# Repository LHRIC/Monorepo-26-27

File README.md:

# LHRIC Monorepo 26/27

This is the Monorepo containing all of the code for the LHRIC 26/27 season.
Documentation is hosted at a GitHub pages site for this repository. If you're
looking for a broad overview of projects look in the confluence and if you're
looking for specific details about implementations, look at the GitHub pages docs.

Check the [documentation website](https://lhric.github.io/Monorepo-26-27/) for more info.

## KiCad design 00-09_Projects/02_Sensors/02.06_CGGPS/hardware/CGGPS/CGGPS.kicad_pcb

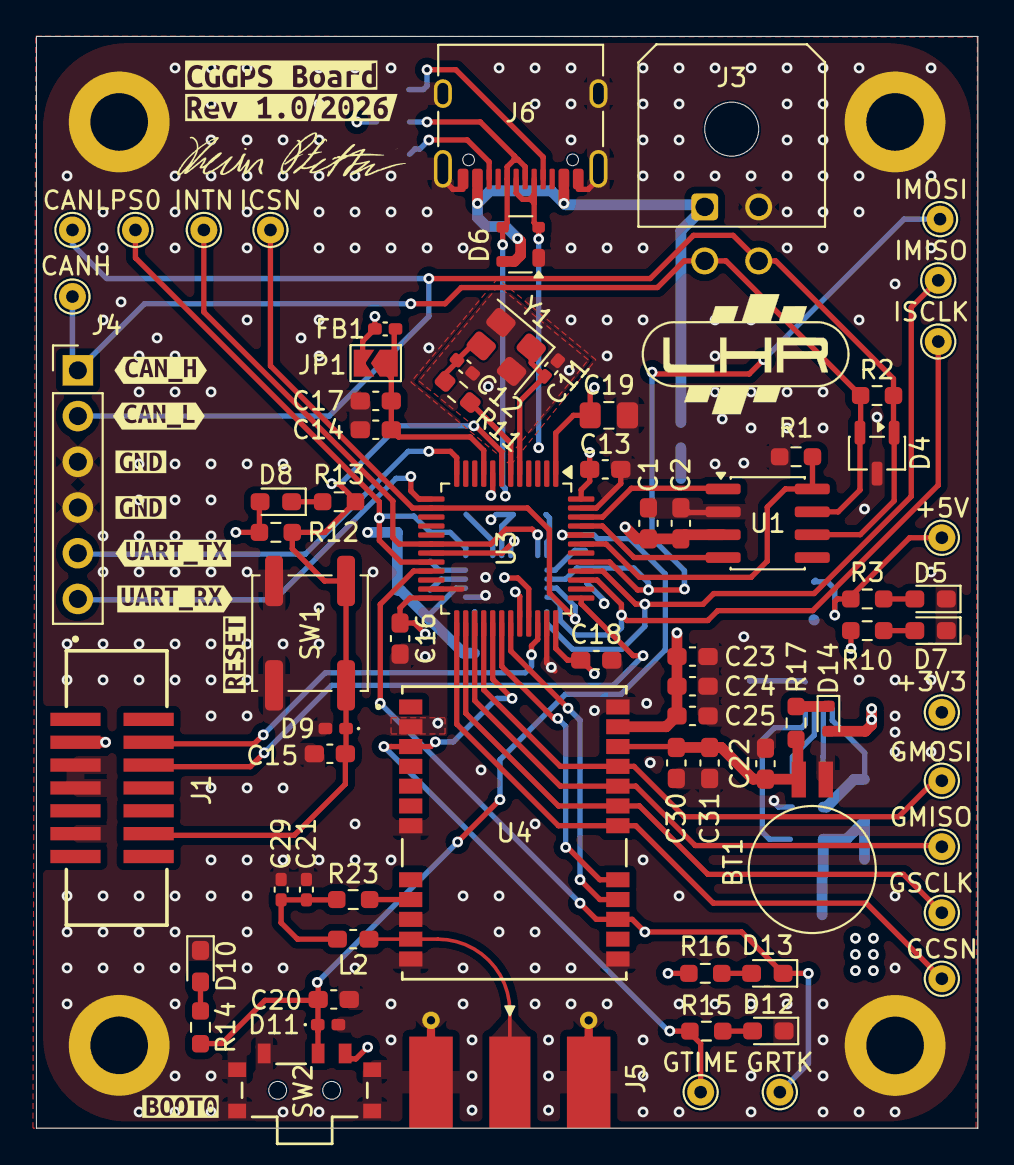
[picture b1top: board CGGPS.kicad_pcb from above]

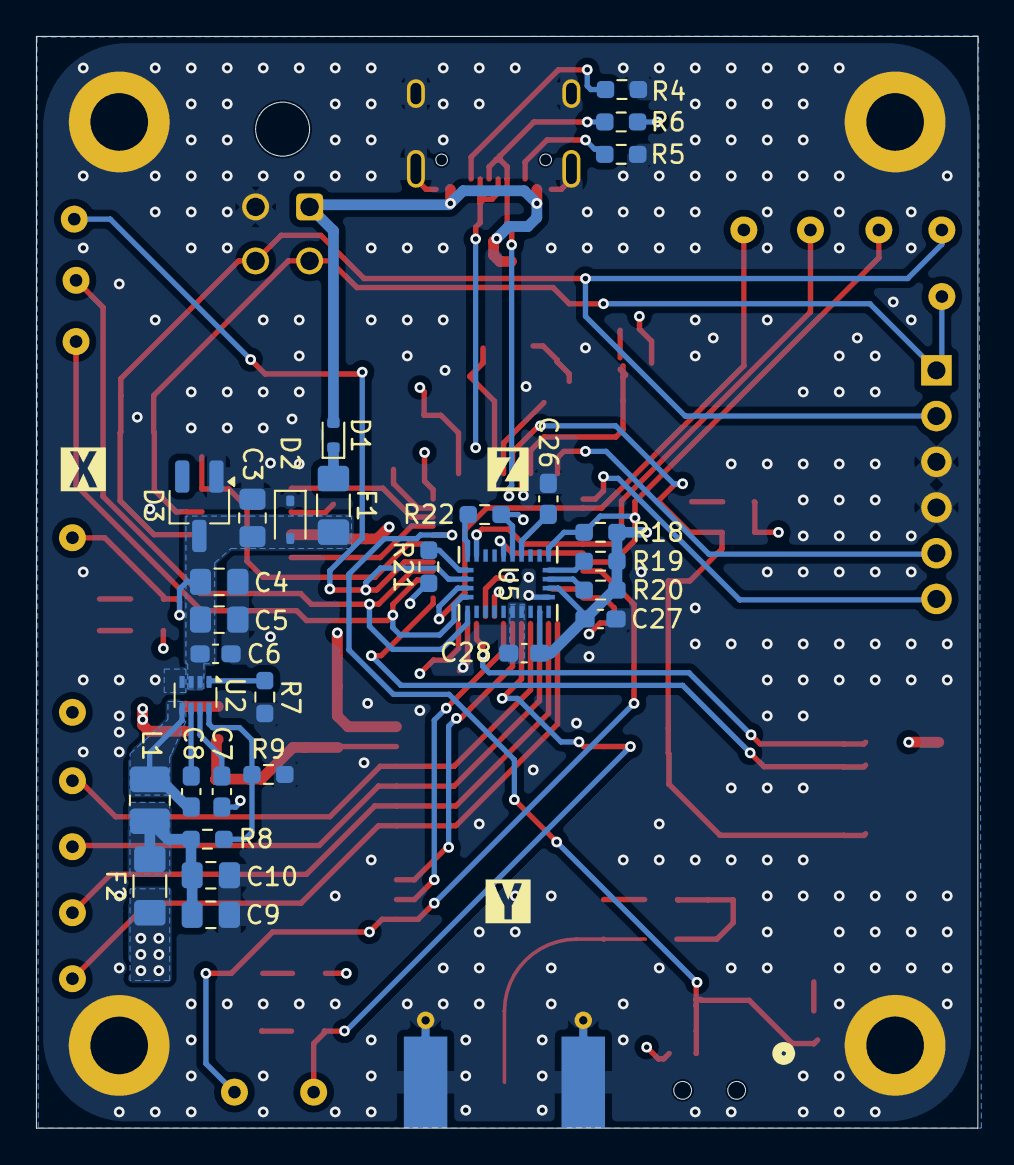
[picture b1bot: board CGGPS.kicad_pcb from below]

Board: 4 copper layers, 52.3 x 60.6 mm, 122 parts (33 on the bottom side), 61 nets.

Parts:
+3V3, +5V: TestPoint; TestPoint_THTPad_D1.5mm_Drill0.7mm
BT1: MS621FE-FL11E; BatteryHolder_Seiko_MS621F
C1, C6, C8, C13, C15, C16, C18, C20, C23, C24, C26, C27, C28: 0.1uF; C_0603_1608Metric_Pad1.08x0.95mm_HandSolder
C2, C17, C22, C25, C30, C31: 1uF; C_0603_1608Metric_Pad1.08x0.95mm_HandSolder
C3: 33uF; C_0805_2012Metric_Pad1.18x1.45mm_HandSolder
C4, C5: 10uF; C_0805_2012Metric_Pad1.18x1.45mm_HandSolder
C7: 33nF; C_0603_1608Metric_Pad1.08x0.95mm_HandSolder
C9, C10: 22uF; C_0805_2012Metric_Pad1.18x1.45mm_HandSolder
C11, C12: 12pF; C_0402_1005Metric_Pad0.74x0.62mm_HandSolder
C14: 10nF; C_0603_1608Metric_Pad1.08x0.95mm_HandSolder
C19: 4.7uF; C_0805_2012Metric_Pad1.18x1.45mm_HandSolder
C21: 47 pF; C_0402_1005Metric_Pad0.74x0.62mm_HandSolder
C29: 100nF; C_0402_1005Metric_Pad0.74x0.62mm_HandSolder
CANH: TestPoint; TestPoint_THTPad_D1.5mm_Drill0.7mm
CANL: TestPoint; TestPoint_THTPad_D1.5mm_Drill0.7mm
D1, D14: SDM20U30-7; D_SOD-523
D2: SD05C-01F; D_SOD-323
D3: SZBZX84C5V1LT1G; SC-59_Handsoldering
D4: ESD2CAN24DBZRQ1; SOT-23-3
D5, D7, D13: LED_GREEN; D_0603_1608Metric_Pad1.05x0.95mm_HandSolder
D6: PRTR5V0U2X; SOT-143
D8: LED_RED; D_0603_1608Metric_Pad1.05x0.95mm_HandSolder
D9, D11: ACPDQC3V3T-HF; D_0402_1005Metric_Pad0.77x0.64mm_HandSolder
D10: LED_AMBER; D_0603_1608Metric_Pad1.05x0.95mm_HandSolder
D12: LED_BLUE; D_0603_1608Metric_Pad1.05x0.95mm_HandSolder
F1: 0.5A; Fuse_1206_3216Metric_Pad1.42x1.75mm_HandSolder
F2: 750mA; Fuse_1206_3216Metric_Pad1.42x1.75mm_HandSolder
FB1: FerriteBead; L_0402_1005Metric_Pad0.77x0.64mm_HandSolder
GCSN: TestPoint; TestPoint_THTPad_D1.5mm_Drill0.7mm
GMISO: TestPoint; TestPoint_THTPad_D1.5mm_Drill0.7mm
GMOSI: TestPoint; TestPoint_THTPad_D1.5mm_Drill0.7mm
GRTK: TestPoint; TestPoint_THTPad_D1.5mm_Drill0.7mm
GSCLK: TestPoint; TestPoint_THTPad_D1.5mm_Drill0.7mm
GTIME: TestPoint; TestPoint_THTPad_D1.5mm_Drill0.7mm
H1, H2, H3, H4: MountingHole_Pad; MountingHole_3.2mm_M3_DIN965_Pad
ICSN: TestPoint; TestPoint_THTPad_D1.5mm_Drill0.7mm
IMISO: TestPoint; TestPoint_THTPad_D1.5mm_Drill0.7mm
IMOSI: TestPoint; TestPoint_THTPad_D1.5mm_Drill0.7mm
INTN: TestPoint; TestPoint_THTPad_D1.5mm_Drill0.7mm
ISCLK: TestPoint; TestPoint_THTPad_D1.5mm_Drill0.7mm
J1: SHF-107-01-L-D-SM; SAMTEC_SHF-107-01-L-D-SM
J3: Conn_01x04_Socket; Molex_Micro-Fit_3.0_43045-0400_2x02_P3.00mm_Horizontal
J4: Conn_01x06_Pin; PinHeader_1x06_P2.54mm_Vertical
J5: Conn_Coaxial; SMA_Molex_73251-1153_EdgeMount_Horizontal
J6: USB_C_Receptacle_USB2.0_16P; USB_C_Receptacle_XKB_U262-16XN-4BVC11
JP1: SolderJumper_2_Open; SolderJumper-2_P1.3mm_Open_TrianglePad1.0x1.5mm
L1: 1uH; L_1008_2520Metric_Pad1.43x2.20mm_HandSolder
L2: 120 nH; L_0603_1608Metric_Pad1.05x0.95mm_HandSolder
PS0: TestPoint; TestPoint_THTPad_D1.5mm_Drill0.7mm
R1, R7, R9, R12, R18, R19, R20: 10k; R_0603_1608Metric_Pad0.98x0.95mm_HandSolder
R2: 120; R_0603_1608Metric_Pad0.98x0.95mm_HandSolder
R3, R10, R13, R14: 330; R_0603_1608Metric_Pad0.98x0.95mm_HandSolder
R4, R5: 5.1k; R_0603_1608Metric_Pad0.98x0.95mm_HandSolder
R6: 1.5k; R_0603_1608Metric_Pad0.98x0.95mm_HandSolder
R8: 31.6k; R_0603_1608Metric_Pad0.98x0.95mm_HandSolder
R11, R15, R16: 220; R_0603_1608Metric_Pad0.98x0.95mm_HandSolder
R17: 620; R_0603_1608Metric_Pad0.98x0.95mm_HandSolder
R21, R22: 4.7k; R_0603_1608Metric_Pad0.98x0.95mm_HandSolder
R23: 15; R_0603_1608Metric_Pad0.98x0.95mm_HandSolder
SW1: PTS645SH43SMTR92 LFS; SW_Push_1P1T_NO_CK_KSC7xxJ
SW2: 450404015514; WS-SLSU_6p7x2p7_WRE
U1: SN65HVD230; SOIC-8_3.9x4.9mm_P1.27mm
U2: TPS62933DRLR; SOT-583-8
U3: STM32F302C8Tx; LQFP-48_7x7mm_P0.5mm
U4: NEO-F9P-15B
U5: BNO086; BN0086_1_LGA-28_CEV
Y1: RH100-16.000-9-1010-TR; Crystal_SMD_WE_CFPX-180-4Pin_3.2x2.5mm
kibuzzard-6AEAD634, kibuzzard-6AEAD634#2: G***; kibuzzard-6AEAD634
kibuzzard-6AEAD642: G***; kibuzzard-6AEAD642
kibuzzard-6AEAD654: G***; kibuzzard-6AEAD654
kibuzzard-6AEAD677: G***; kibuzzard-6AEAD677
kibuzzard-6AEAD693: G***; kibuzzard-6AEAD693
kibuzzard-6AEAD714: G***; kibuzzard-6AEAD714
kibuzzard-6AEADD88: G***; kibuzzard-6AEADD88
kibuzzard-6AEF8D4C: G***; kibuzzard-6AEF8D4C
kibuzzard-6AEF8E55: G***; kibuzzard-6AEF8E55
kibuzzard-6AEFA2AB: G***; kibuzzard-6AEFA2AB
kibuzzard-6AEFA2BC: G***; kibuzzard-6AEFA2BC
kibuzzard-6AEFA2C8: G***; kibuzzard-6AEFA2C8
kibuzzard-6AEFC3E2: G***; kibuzzard-6AEFC3E2

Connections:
+3.3V: +3V3.1 (1_1), C1.1, C2.1, C13.1, C16.1, C18.1, C19.1, C23.1, C24.1, C25.1, C27.1, C28.1, D8.2 (A), D14.2 (A), F2.2, FB1.2, J1.03, JP1.2 (B), R6.1, R10.1, R12.1, R16.1, R18.1, R19.1, R20.1, R21.1, R22.1, SW2.3 (A), U1.3 (VCC), U3.1 (VBAT), U3.24 (VDD), U3.36 (VDD), U3.48 (VDD), U4.23 (VCC), U5.3 (VDD), U5.10 (CLKSEL0), U5.28 (VDDIO)
+3.3VA: C14.1, C17.1, FB1.1, JP1.1 (A), U3.9 (VDDA)
+5V: +5V.1 (1_1), C3.1, C4.1, C5.1, C6.1, D2.2 (A2), D3.3 (K), F1.2, R3.1, U2.2 (EN), U2.3 (VIN)
+VBUS: D1.2 (A), D6.4 (VCC), J3.1, J6.A4 (VBUS), J6.A9 (VBUS), J6.B4 (VBUS), J6.B9 (VBUS)
/CAN_H: CANH.1 (1_1), D4.2, J3.3, J4.1, R2.1, U1.7 (CANH)
/CAN_L: CANL.1 (1_1), D4.1, J3.4, J4.2, R2.2, U1.6 (CANL)
/CAN_RX: U1.4 (R), U3.45 (PB8)
/CAN_SLEEP: R1.1, U1.8 (Rs), U3.43 (PB7)
/CAN_TX: U1.1 (D), U3.46 (PB9)
/GPS/V_BACKUP: BT1.1 (+), C22.1, C30.1, C31.1, R17.2, U4.22 (V_BCKP)
/GPS_CS_N: GCSN.1 (1_1), U3.25 (PB12), U4.18 (SDA/SPI_CS_N)
/GPS_MISO: GMISO.1 (1_1), U3.27 (PB14), U4.20 (TXD/SPI_SDO)
/GPS_MOSI: GMOSI.1 (1_1), U3.28 (PB15), U4.21 (RXD/SPI_SDI)
/GPS_RTK_STATUS: D13.1 (K), GRTK.1 (1_1), U3.21 (PB10), U4.15 (RTK_STAT)
/GPS_SCLK: GSCLK.1 (1_1), U3.26 (PB13), U4.19 (SCL/SPI_SLK)
/GPS_TIMEPULSE: GTIME.1 (1_1), R15.1, U3.29 (PA8), U4.3 (TIMEPULSE)
/GPS_USART_RX: U3.31 (PA10), U4.16 (TXD2)
/GPS_USART_TX: U3.30 (PA9), U4.17 (RXD2)
/IMU_BOOTN: R20.2, U5.4 (BOOTN)
/IMU_CS_N: ICSN.1 (1_1), U3.14 (PA4), U5.18 (H_CSN)
/IMU_H_INTN: INTN.1 (1_1), U3.18 (PB0), U5.14 (H_INTN)
/IMU_MISO: IMISO.1 (1_1), U3.40 (PB4), U5.20 (H_SDA/H_MISO/TX)
/IMU_MOSI: IMOSI.1 (1_1), U3.41 (PB5), U5.17 (SA0/H_MOSI)
/IMU_NRST: U3.19 (PB1), U5.11 (NRST)
/IMU_PSO/WAKE: PS0.1 (1_1), R18.2, U3.20 (PB2), U5.6 (PS0/WAKE)
/IMU_SCLK: ISCLK.1 (1_1), U3.39 (PB3), U5.19 (H_SCL/SCK/RX)
/MCU/BOOT0: C20.1, D11.1 (K), R14.1, SW2.2 (B), U3.44 (BOOT0)
/MCU/RCC_OSC_IN: C11.1, U3.5 (PF0), Y1.1
/MCU/RCC_OSC_OUT: R11.2, U3.6 (PF1)
/MCU_NRST: C15.1, D9.1 (K), J1.12, R12.2, R13.2, SW1.1, U3.7 (NRST)
/SWCLK: J1.06, U3.37 (PA14)
/SWDIO: J1.04, U3.34 (PA13)
/USART2_RX: J4.6, U3.13 (PA3)
/USART2_TX: J4.5, U3.12 (PA2)
/USB_DM: D6.2 (I/O1), J6.A7 (D-), J6.B7 (D-), U3.32 (PA11)
/USB_DP: D6.3 (I/O2), J6.A6 (D+), J6.B6 (D+), R6.2, U3.33 (PA12)
GND: BT1.2 (-), C1.2, C2.2, C3.2, C4.2, C5.2, C6.2, C7.2, C9.2, C10.2, C11.2, C12.2, C13.2, C14.2, C15.2, C16.2, C17.2, C18.2, C19.2, C20.2, C21.1, C22.2, C23.2, C24.2, C25.2, C26.2, C27.2, C28.2, C29.1, C30.2, C31.2, D2.1 (A1), D3.1 (A), D4.3, D5.1 (K), D6.1 (GND), D7.1 (K), D9.2 (A), D10.1 (K), D11.2 (A), D12.1 (K), H1.1 (1_1), H2.1 (1_1), H3.1 (1_1), H4.1 (1_1), J1.05, J1.07, J1.11, J3.2, J4.3, J4.4, J5.2 (Ext), J6.A1 (GND), J6.A12 (GND), J6.B1 (GND), J6.B12 (GND), J6.SH (SHIELD), R1.2, R4.2, R5.2, R7.2, R9.2, SW1.2, SW2.1 (C), SW2.4 (MP), SW2.5 (MP), SW2.6 (MP), SW2.7 (MP), U1.2 (GND), U2.4 (GND), U3.8 (VSSA), U3.23 (VSS), U3.35 (VSS), U3.47 (VSS), U4.2 (D_SEL), U4.7 (VDD_USB), U4.10 (GND), U4.12 (GND), U4.13 (GND), U4.24 (GND), U5.2 (GND), U5.25 (GND), U5.26 (XOUT32/CLKSEL1), Y1.2 (G), Y1.4 (G)
unnamed: C9.1, C10.1, F2.1, L1.2, R8.1
unnamed: C12.1, R11.1, Y1.3
unnamed: C21.2, C29.2, L2.2, R23.1
unnamed: D1.1 (K), F1.1
unnamed: D5.2 (A), R3.2
unnamed: D7.2 (A), R10.2
unnamed: D8.1 (K), R13.1
unnamed: D10.2 (A), R14.2
unnamed: D12.2 (A), R15.2
unnamed: D13.2 (A), R16.2
unnamed: D14.1 (K), R17.1
unnamed: J5.1 (In), L2.1, U4.11 (RF_IN)
unnamed: J6.A5 (CC1), R4.1
unnamed: J6.B5 (CC2), R5.1
unnamed: C8.1, U2.6 (BST)
unnamed: R8.2, R9.1, U2.8 (FB)
unnamed: R7.1, U2.1 (RT)
unnamed: C7.1, U2.7 (SS)
unnamed: C8.2, L1.1, U2.5 (SW)
unnamed: R23.2, U4.9 (VCC_RF)
unnamed: C26.1, U5.9 (CAP)
unnamed: R22.2, U5.15 (ENV_SCL)
unnamed: R21.2, U5.16 (ENV_SDA)
unnamed: R19.2, U5.5 (PS1)

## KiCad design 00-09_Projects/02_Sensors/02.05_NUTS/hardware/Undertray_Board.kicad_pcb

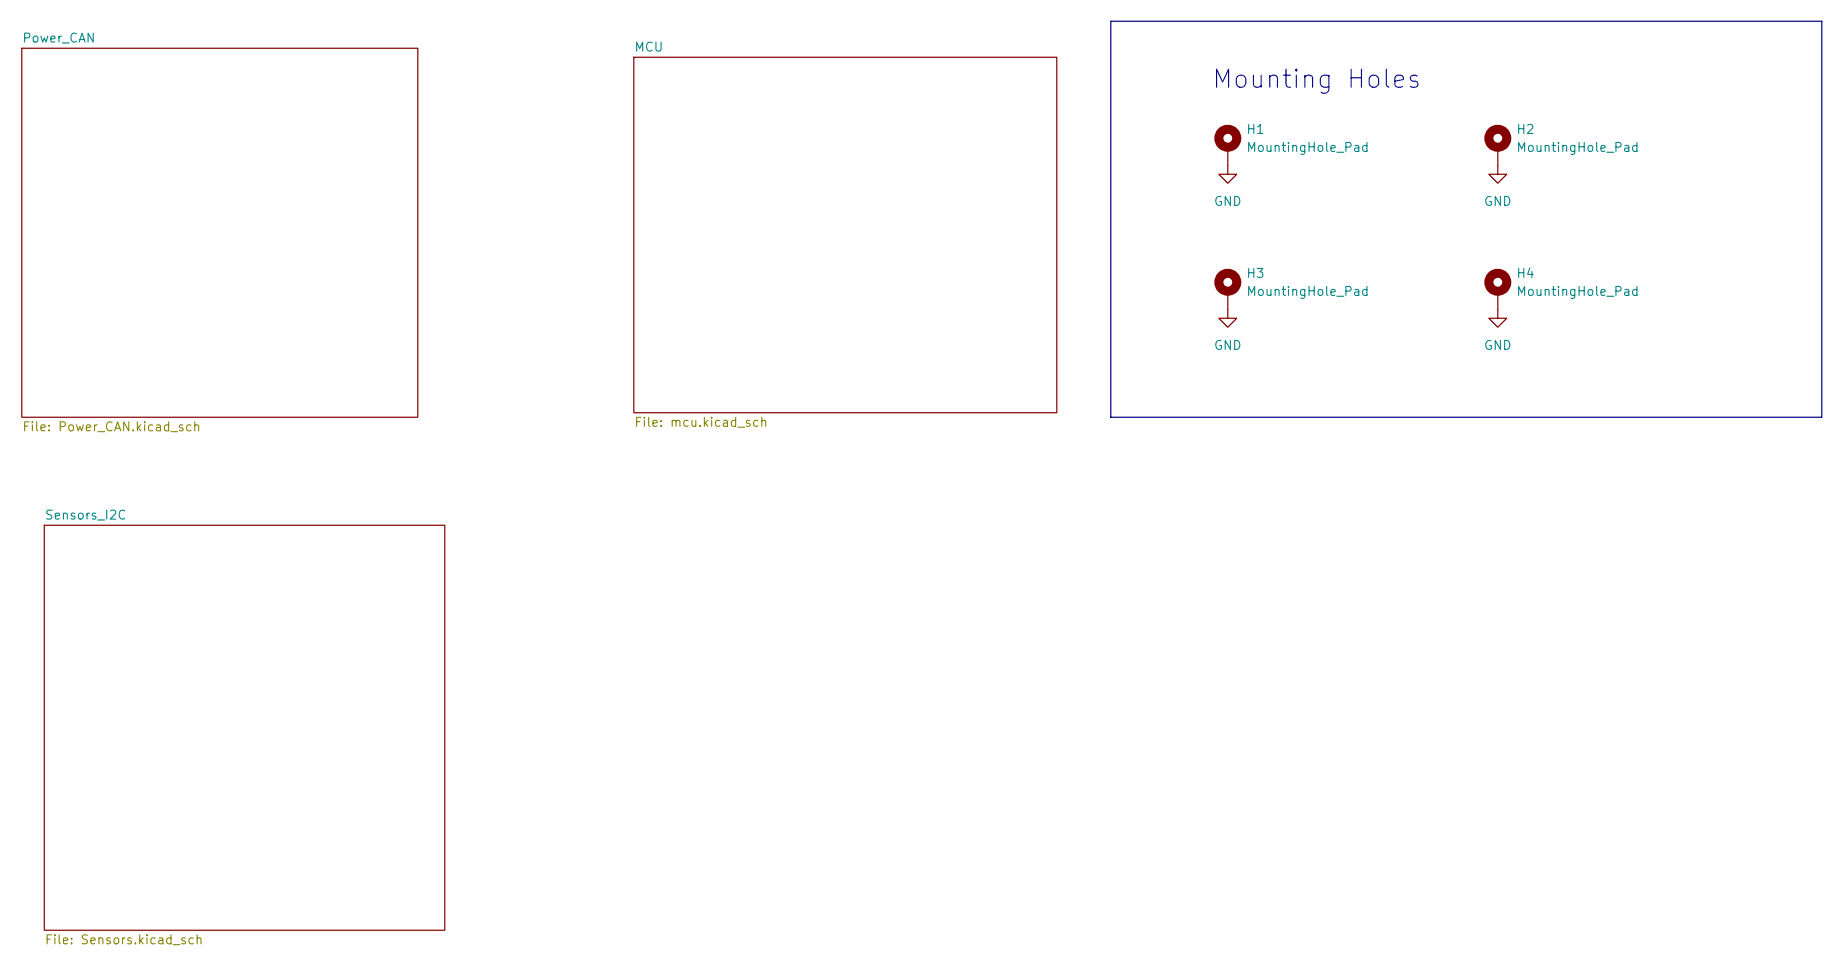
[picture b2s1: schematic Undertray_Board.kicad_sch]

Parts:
H1, H2, H3, H4: MountingHole_Pad; MountingHole_3.2mm_M3_DIN965_Pad

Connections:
GND: H1.1 (1_1), H2.1 (1_1), H3.1 (1_1), H4.1 (1_1); also elsewhere on the board

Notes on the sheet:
Mounting Holes

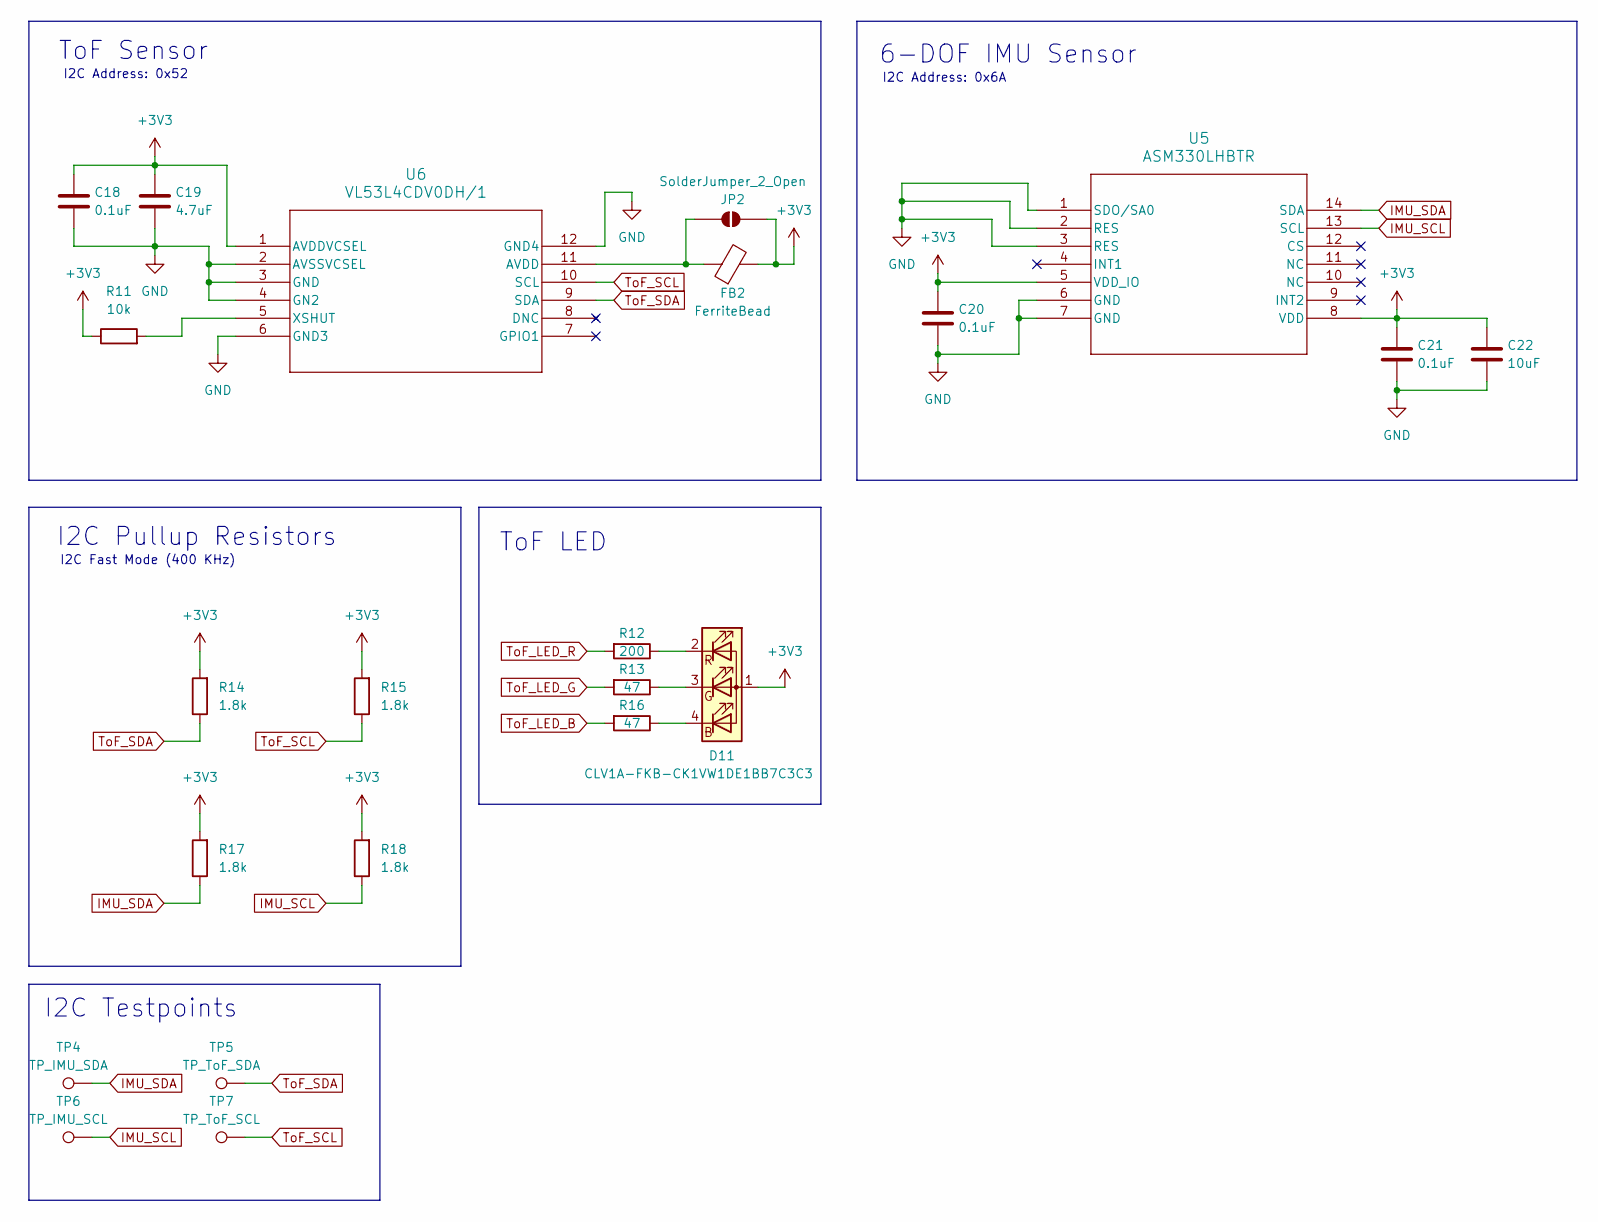
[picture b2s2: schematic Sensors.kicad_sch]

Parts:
C18, C20, C21: 0.1uF; C_0603_1608Metric_Pad1.08x0.95mm_HandSolder
C19: 4.7uF; C_0805_2012Metric_Pad1.18x1.45mm_HandSolder
C22: 10uF; C_0805_2012Metric_Pad1.18x1.45mm_HandSolder
D11: CLV1A-FKB-CK1VW1DE1BB7C3C3; LED_Cree-PLCC4_3.2x2.8mm_CCW
FB2: FerriteBead; L_0402_1005Metric_Pad0.77x0.64mm_HandSolder
JP2: SolderJumper_2_Open; SolderJumper-2_P1.3mm_Open_TrianglePad1.0x1.5mm
R11: 10k; R_0603_1608Metric_Pad0.98x0.95mm_HandSolder
R12: 200; R_0603_1608Metric_Pad0.98x0.95mm_HandSolder
R13, R16: 47; R_0603_1608Metric_Pad0.98x0.95mm_HandSolder
R14, R15, R17, R18: 1.8k; R_0603_1608Metric_Pad0.98x0.95mm_HandSolder
TP4: TP_IMU_SDA; TestPoint_THTPad_D1.5mm_Drill0.7mm
TP5: TP_ToF_SDA; TestPoint_THTPad_D1.5mm_Drill0.7mm
TP6: TP_IMU_SCL; TestPoint_THTPad_D1.5mm_Drill0.7mm
TP7: TP_ToF_SCL; TestPoint_THTPad_D1.5mm_Drill0.7mm
U5: ASM330LHBTR; LGA-14L_2p5x3-0p5_STM-M
U6: VL53L4CDV0DH/1; LGA12_STM

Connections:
+3V3: C18.1, C19.1, C20.1, C21.1, C22.1, D11.1 (A), FB2.2, JP2.2 (B), R11.1, R14.2, R15.2, R17.2, R18.2, U5.5 (VDD_IO), U5.8 (VDD), U6.1 (AVDDVCSEL); also elsewhere on the board
GND: C18.2, C19.2, C20.2, C21.2, C22.2, U5.1 (SDO/SA0), U5.2 (RES), U5.3 (RES), U5.6 (GND), U5.7 (GND), U6.2 (AVSSVCSEL), U6.3 (GND), U6.4 (GN2), U6.6 (GND3), U6.12 (GND4); also elsewhere on the board
IMU_SCL: R18.1, TP6.1, U5.13 (SCL); also elsewhere on the board
IMU_SDA: R17.1, TP4.1, U5.14 (SDA); also elsewhere on the board
unnamed: D11.4 (BK), R16.1
unnamed: D11.3 (GK), R13.1
unnamed: D11.2 (RK), R12.1
unnamed: FB2.1, JP2.1 (A), U6.11 (AVDD)
unnamed: R11.2, U6.5 (XSHUT)
ToF_LED_B: R16.2; also elsewhere on the board
ToF_LED_G: R13.2; also elsewhere on the board
ToF_LED_R: R12.2; also elsewhere on the board
ToF_SCL: R15.1, TP7.1, U6.10 (SCL); also elsewhere on the board
ToF_SDA: R14.1, TP5.1, U6.9 (SDA); also elsewhere on the board

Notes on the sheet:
6-DOF IMU Sensor
I2C Address: 0x52
I2C Fast Mode (400 KHz)
I2C Address: 0x6A
I2C Testpoints
ToF Sensor
ToF LED
I2C Pullup Resistors

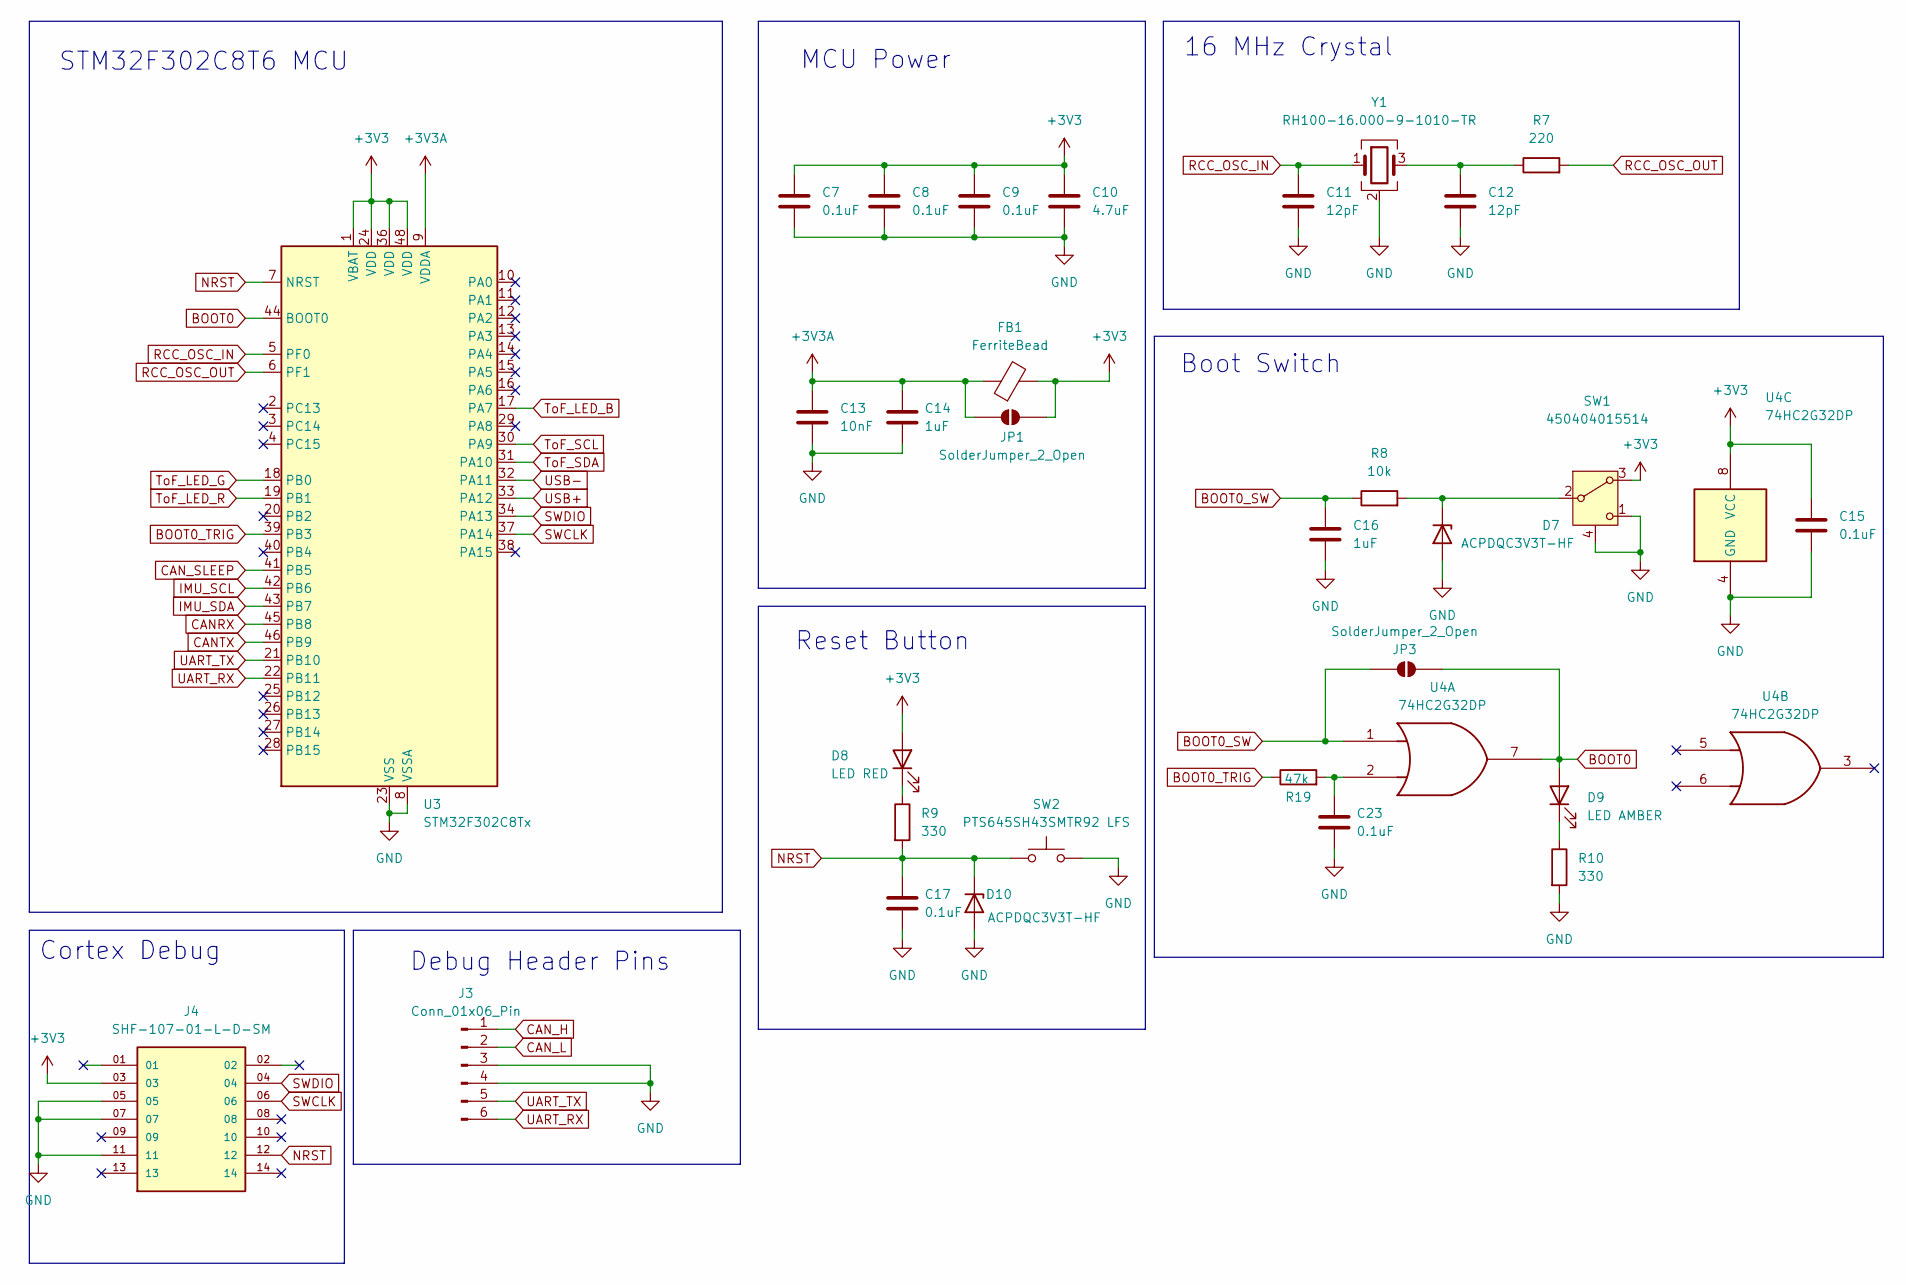
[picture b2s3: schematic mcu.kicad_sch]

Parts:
C7, C8, C9, C15, C17, C23: 0.1uF; C_0603_1608Metric_Pad1.08x0.95mm_HandSolder
C10: 4.7uF; C_0805_2012Metric_Pad1.18x1.45mm_HandSolder
C11, C12: 12pF; C_0402_1005Metric_Pad0.74x0.62mm_HandSolder
C13: 10nF; C_0603_1608Metric_Pad1.08x0.95mm_HandSolder
C14, C16: 1uF; C_0603_1608Metric_Pad1.08x0.95mm_HandSolder
D7, D10: ACPDQC3V3T-HF; D_0402_1005Metric_Pad0.77x0.64mm_HandSolder
D8: LED RED; LED_0603_1608Metric_Pad1.05x0.95mm_HandSolder
D9: LED AMBER; LED_0603_1608Metric_Pad1.05x0.95mm_HandSolder
FB1: FerriteBead; L_0402_1005Metric_Pad0.77x0.64mm_HandSolder
J3: Conn_01x06_Pin; PinHeader_1x06_P2.54mm_Vertical
J4: SHF-107-01-L-D-SM; SAMTEC_SHF-107-01-L-D-SM; PARTREV R
JP1, JP3: SolderJumper_2_Open; SolderJumper-2_P1.3mm_Open_TrianglePad1.0x1.5mm
R7: 220; R_0603_1608Metric_Pad0.98x0.95mm_HandSolder
R8: 10k; R_0603_1608Metric_Pad0.98x0.95mm_HandSolder
R9, R10: 330; R_0603_1608Metric_Pad0.98x0.95mm_HandSolder
R19: 47k; R_0402_1005Metric_Pad0.72x0.64mm_HandSolder
SW1: 450404015514; WS-SLSU_6p7x2p7_WRE
SW2: PTS645SH43SMTR92 LFS; SW_Push_1P1T_NO_CK_KSC7xxJ
U3: STM32F302C8Tx; LQFP-48_7x7mm_P0.5mm
U4: 74HC2G32DP; TSSOP-8_3x3mm_P0.65mm
Y1: RH100-16.000-9-1010-TR; Crystal_SMD_WE_CFPX-180-4Pin_3.2x2.5mm

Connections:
+3V3: C7.1, C8.1, C9.1, C10.1, C15.1, D8.2 (A), FB1.2, J4.03, JP1.2 (B), SW1.3 (A), U3.1 (VBAT), U3.24 (VDD), U3.36 (VDD), U3.48 (VDD), U4.8 (VCC); also elsewhere on the board
+3V3A: C13.1, C14.1, FB1.1, JP1.1 (A), U3.9 (VDDA)
BOOT0: D9.2 (A), JP3.1 (A), U3.44 (BOOT0), U4.7
BOOT0_SW: C16.1, JP3.2 (B), R8.1, U4.1
BOOT0_TRIG: R19.1, U3.39 (PB3)
CANRX: U3.45 (PB8); also elsewhere on the board
CANTX: U3.46 (PB9); also elsewhere on the board
CAN_H: J3.1; also elsewhere on the board
CAN_L: J3.2; also elsewhere on the board
CAN_SLEEP: U3.41 (PB5); also elsewhere on the board
GND: C7.2, C8.2, C9.2, C10.2, C11.2, C12.2, C13.2, C14.2, C15.2, C16.2, C17.2, C23.2, D7.2 (A), D10.2 (A), J3.3, J3.4, J4.05, J4.07, J4.11, R10.2, SW1.1 (C), SW1.4 (MP), SW1.5 (MP), SW1.6 (MP), SW1.7 (MP), SW2.2, U3.8 (VSSA), U3.23 (VSS), U3.35 (VSS), U3.47 (VSS), U4.4 (GND), Y1.2 (G), Y1.4 (G); also elsewhere on the board
IMU_SCL: U3.42 (PB6); also elsewhere on the board
IMU_SDA: U3.43 (PB7); also elsewhere on the board
NRST: C17.1, D10.1 (K), J4.12, R9.2, SW2.1, U3.7 (NRST)
unnamed: C12.1, R7.1, Y1.3
unnamed: C23.1, R19.2, U4.2
unnamed: D7.1 (K), R8.2, SW1.2 (B)
unnamed: D8.1 (K), R9.1
unnamed: D9.1 (K), R10.1
RCC_OSC_IN: C11.1, U3.5 (PF0), Y1.1
RCC_OSC_OUT: R7.2, U3.6 (PF1)
SWCLK: J4.06, U3.37 (PA14)
SWDIO: J4.04, U3.34 (PA13)
ToF_LED_B: U3.17 (PA7); also elsewhere on the board
ToF_LED_G: U3.18 (PB0); also elsewhere on the board
ToF_LED_R: U3.19 (PB1); also elsewhere on the board
ToF_SCL: U3.30 (PA9); also elsewhere on the board
ToF_SDA: U3.31 (PA10); also elsewhere on the board
UART_RX: J3.6, U3.22 (PB11)
UART_TX: J3.5, U3.21 (PB10)
USB+: U3.33 (PA12); also elsewhere on the board
USB-: U3.32 (PA11); also elsewhere on the board

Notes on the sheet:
Reset Button
MCU Power
Cortex Debug
Boot Switch
16 MHz Crystal
STM32F302C8T6 MCU
Debug Header Pins

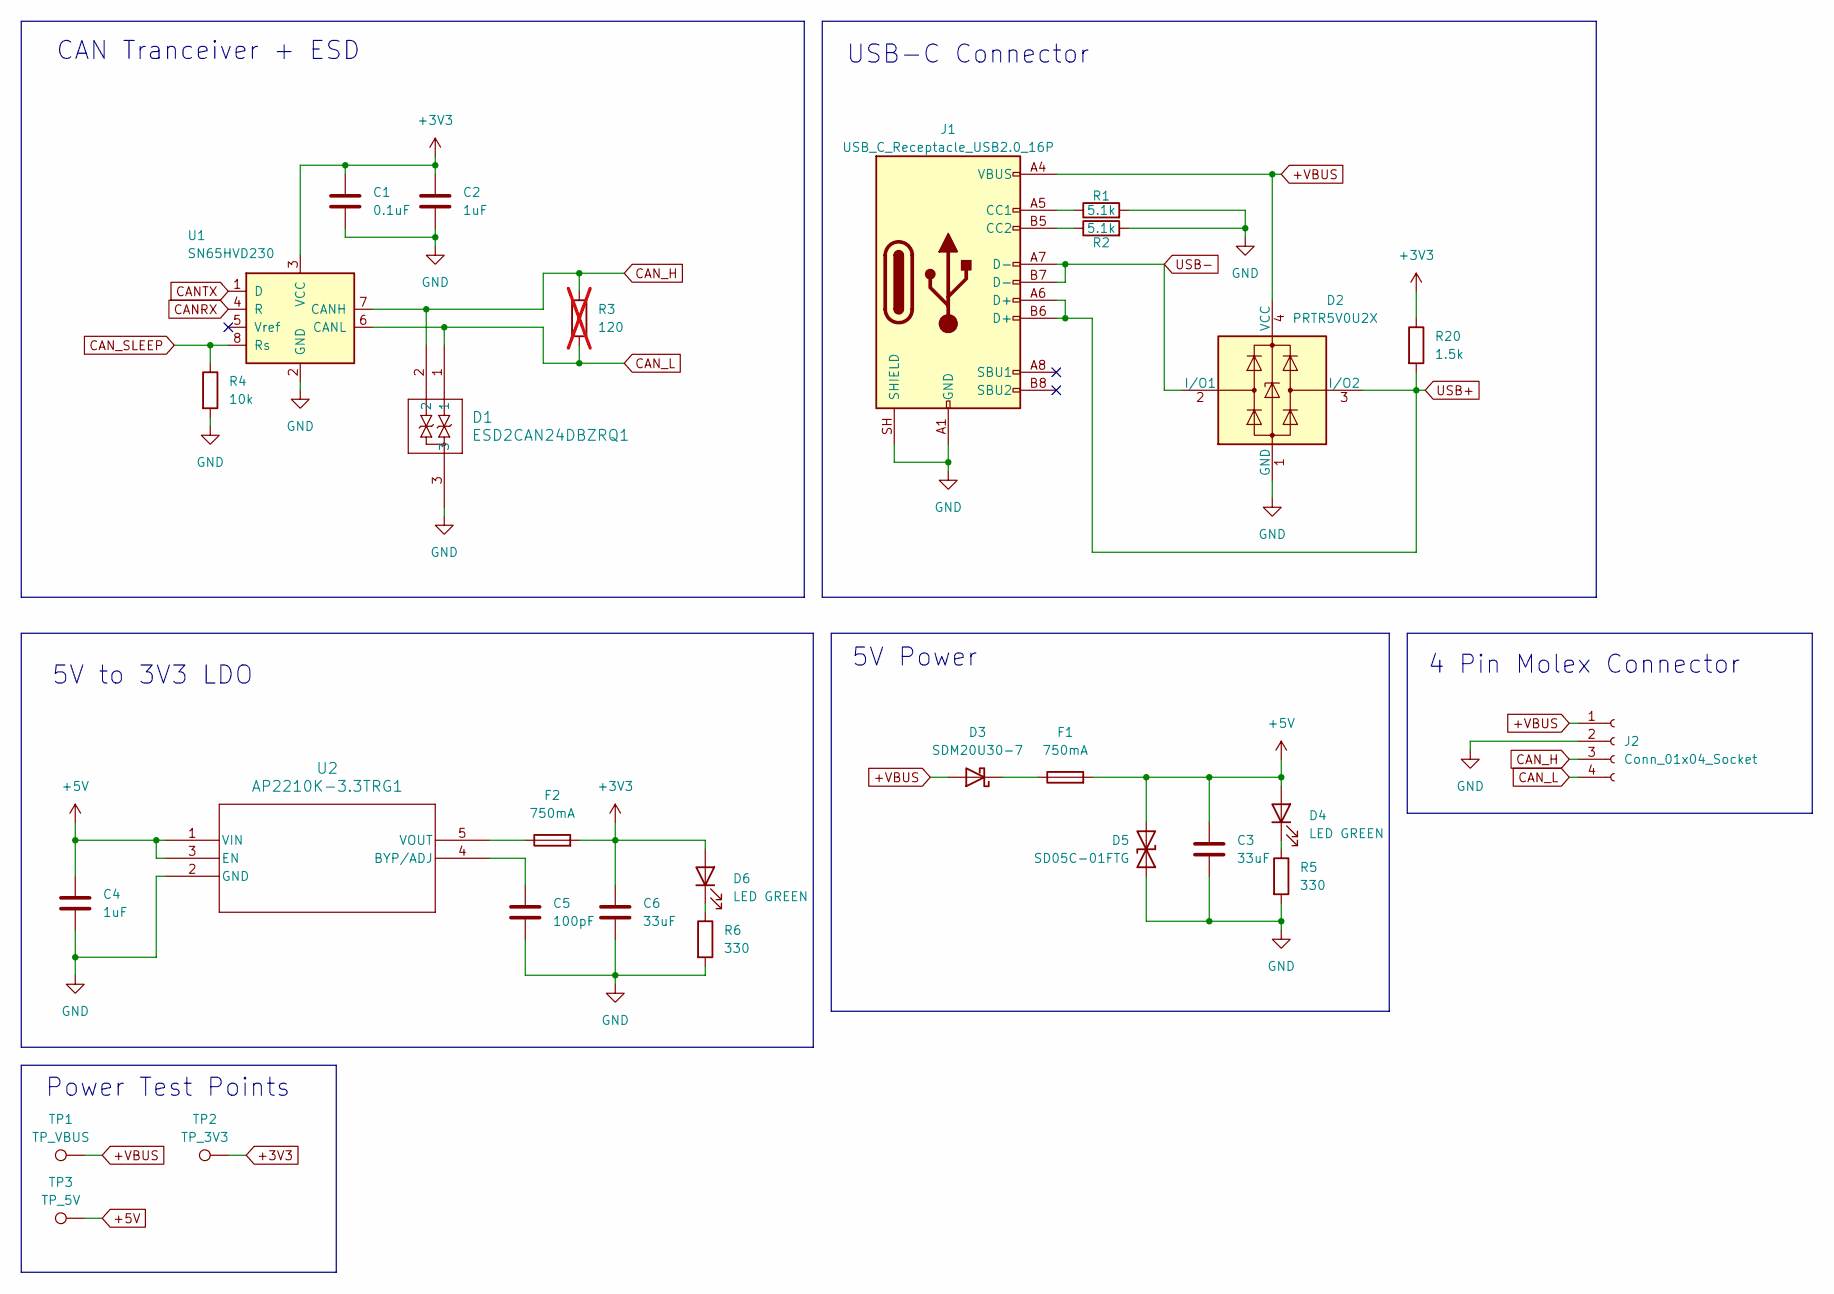
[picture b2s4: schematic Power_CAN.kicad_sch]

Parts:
C1: 0.1uF; C_0603_1608Metric_Pad1.08x0.95mm_HandSolder
C2, C4: 1uF; C_0603_1608Metric_Pad1.08x0.95mm_HandSolder
C3, C6: 33uF; C_0805_2012Metric_Pad1.18x1.45mm_HandSolder
C5: 100pF; C_0805_2012Metric_Pad1.18x1.45mm_HandSolder
D1: ESD2CAN24DBZRQ1; SC-59_Handsoldering
D2: PRTR5V0U2X; SOT-143
D3: SDM20U30-7; D_SOD-523
D4, D6: LED GREEN; LED_0603_1608Metric_Pad1.05x0.95mm_HandSolder
D5: SD05C-01FTG; D_SOD-323_HandSoldering
F1, F2: 750mA; Fuse_1206_3216Metric_Pad1.42x1.75mm_HandSolder
J1: USB_C_Receptacle_USB2.0_16P; USB_C_Receptacle_XKB_U262-16XN-4BVC11
J2: Conn_01x04_Socket; CONN_SD-43045-001_04_MOL
R1, R2: 5.1k; R_0603_1608Metric_Pad0.98x0.95mm_HandSolder
R3: 120; R_0603_1608Metric_Pad0.98x0.95mm_HandSolder; not fitted
R4: 10k; R_0603_1608Metric_Pad0.98x0.95mm_HandSolder
R5, R6: 330; R_0603_1608Metric_Pad0.98x0.95mm_HandSolder
R20: 1.5k; R_0603_1608Metric_Pad0.98x0.95mm_HandSolder
TP1: TP_VBUS; TestPoint_THTPad_D1.5mm_Drill0.7mm
TP2: TP_3V3; TestPoint_THTPad_D1.5mm_Drill0.7mm
TP3: TP_5V; TestPoint_THTPad_D1.5mm_Drill0.7mm
U1: SN65HVD230; SOIC-8_3.9x4.9mm_P1.27mm
U2: AP2210K-3.3TRG1; SOT-23-5_HandSoldering

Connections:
+3V3: C1.1, C2.1, C6.1, D6.2 (A), F2.2, R20.1, U1.3 (VCC); also elsewhere on the board
+5V: C3.1, C4.1, D4.2 (A), D5.2 (A2), F1.2, U2.1 (VIN), U2.3 (EN); also elsewhere on the board
+VBUS: D2.4 (VCC), D3.2 (A), J1.A4 (VBUS), J1.A9 (VBUS), J1.B4 (VBUS), J1.B9 (VBUS), J2.1, TP1.1; also elsewhere on the board
CANRX: U1.4 (R); also elsewhere on the board
CANTX: U1.1 (D); also elsewhere on the board
CAN_H: D1.2, J2.3, R3.1, U1.7 (CANH); also elsewhere on the board
CAN_L: D1.1, J2.4, R3.2, U1.6 (CANL); also elsewhere on the board
CAN_SLEEP: R4.1, U1.8 (Rs); also elsewhere on the board
GND: C1.2, C2.2, C3.2, C4.2, C5.2, C6.2, D1.3, D2.1 (GND), D5.1 (A1), J1.A1 (GND), J1.A12 (GND), J1.B1 (GND), J1.B12 (GND), J1.SH (SHIELD), J2.2, R1.2, R2.2, R4.2, R5.2, R6.2, U1.2 (GND), U2.2 (GND); also elsewhere on the board
unnamed: D3.1 (K), F1.1
unnamed: D4.1 (K), R5.1
unnamed: D6.1 (K), R6.1
unnamed: J1.A5 (CC1), R1.1
unnamed: J1.B5 (CC2), R2.1
unnamed: C5.1, U2.4 (BYP/ADJ)
unnamed: F2.1, U2.5 (VOUT)
USB+: D2.3 (I/O2), J1.A6 (D+), J1.B6 (D+), R20.2; also elsewhere on the board
USB-: D2.2 (I/O1), J1.A7 (D-), J1.B7 (D-); also elsewhere on the board

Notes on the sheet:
USB-C Connector
4 Pin Molex Connector
CAN Tranceiver + ESD
Power Test Points
5V Power
5V to 3V3 LDO

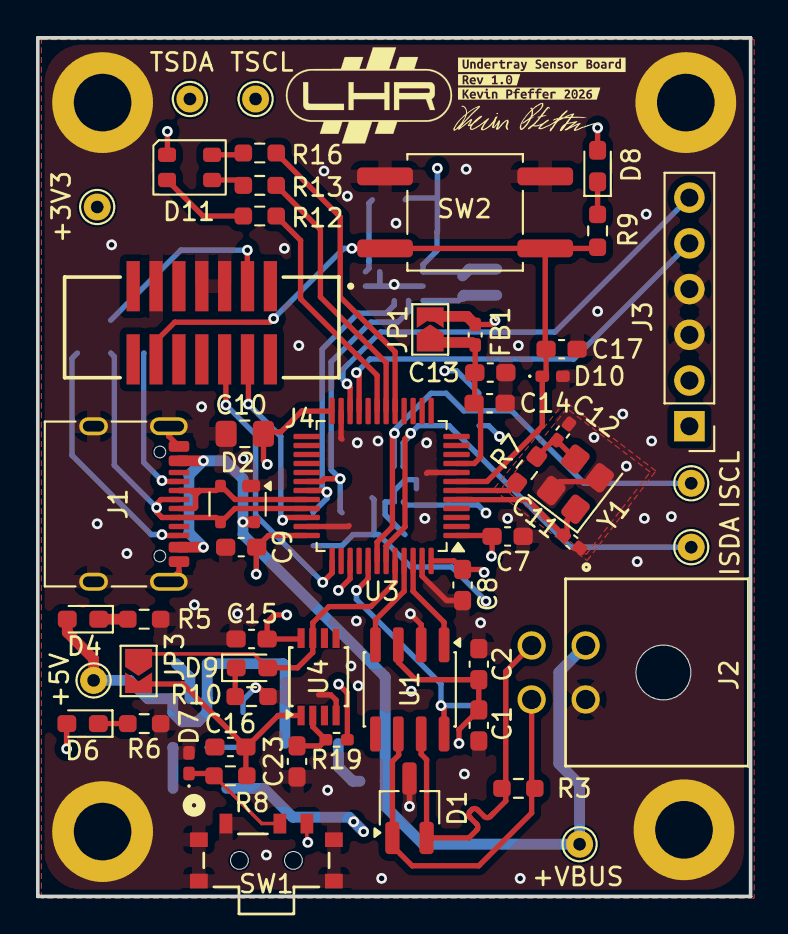
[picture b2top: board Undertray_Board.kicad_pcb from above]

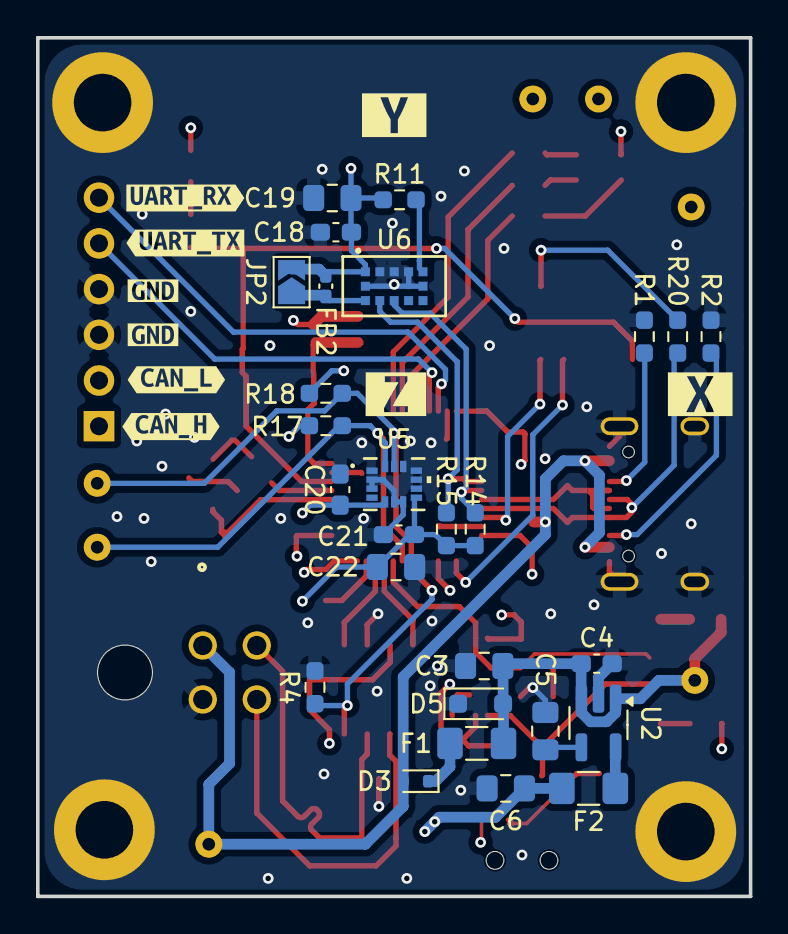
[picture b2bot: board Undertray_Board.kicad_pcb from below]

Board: 4 copper layers, 39.6 x 47.7 mm, 97 parts (36 on the bottom side), 46 nets.

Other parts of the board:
+3V3: TP_3V3; TestPoint_THTPad_D1.5mm_Drill0.7mm
+5V: TP_5V; TestPoint_THTPad_D1.5mm_Drill0.7mm
+VBUS: TP_VBUS; TestPoint_THTPad_D1.5mm_Drill0.7mm
ISCL: TP_IMU_SCL; TestPoint_THTPad_D1.5mm_Drill0.7mm
ISDA: TP_IMU_SDA; TestPoint_THTPad_D1.5mm_Drill0.7mm
TSCL: TP_ToF_SCL; TestPoint_THTPad_D1.5mm_Drill0.7mm
TSDA: TP_ToF_SDA; TestPoint_THTPad_D1.5mm_Drill0.7mm
kibuzzard-6AC1ECA0: G***; kibuzzard-6AC1ECA0
kibuzzard-6AC1EE46: G***; kibuzzard-6AC1EE46
kibuzzard-6AC1EF16: G***; kibuzzard-6AC1EF16
kibuzzard-6AC9A8CB: G***; kibuzzard-6AC9A8CB
kibuzzard-6ACFF7B6: G***; kibuzzard-6ACFF7B6
kibuzzard-6ACFFC7D: G***; kibuzzard-6ACFFC7D
kibuzzard-6AEFC54C, kibuzzard-6AEFC54C#2: G***; kibuzzard-6AEFC54C
kibuzzard-6AEFC560: G***; kibuzzard-6AEFC560
kibuzzard-6AEFC585: G***; kibuzzard-6AEFC585
kibuzzard-6AEFC616: G***; kibuzzard-6AEFC616
kibuzzard-6AF0E7F2: G***; kibuzzard-6AF0E7F2

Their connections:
+3V3: +3V3.1 (1_1); also elsewhere on the board
+5V: +5V.1 (1_1); also elsewhere on the board
+VBUS: +VBUS.1 (1_1); also elsewhere on the board
IMU_SCL: ISCL.1 (1_1); also elsewhere on the board
IMU_SDA: ISDA.1 (1_1); also elsewhere on the board
ToF_SCL: TSCL.1 (1_1); also elsewhere on the board
ToF_SDA: TSDA.1 (1_1); also elsewhere on the board
